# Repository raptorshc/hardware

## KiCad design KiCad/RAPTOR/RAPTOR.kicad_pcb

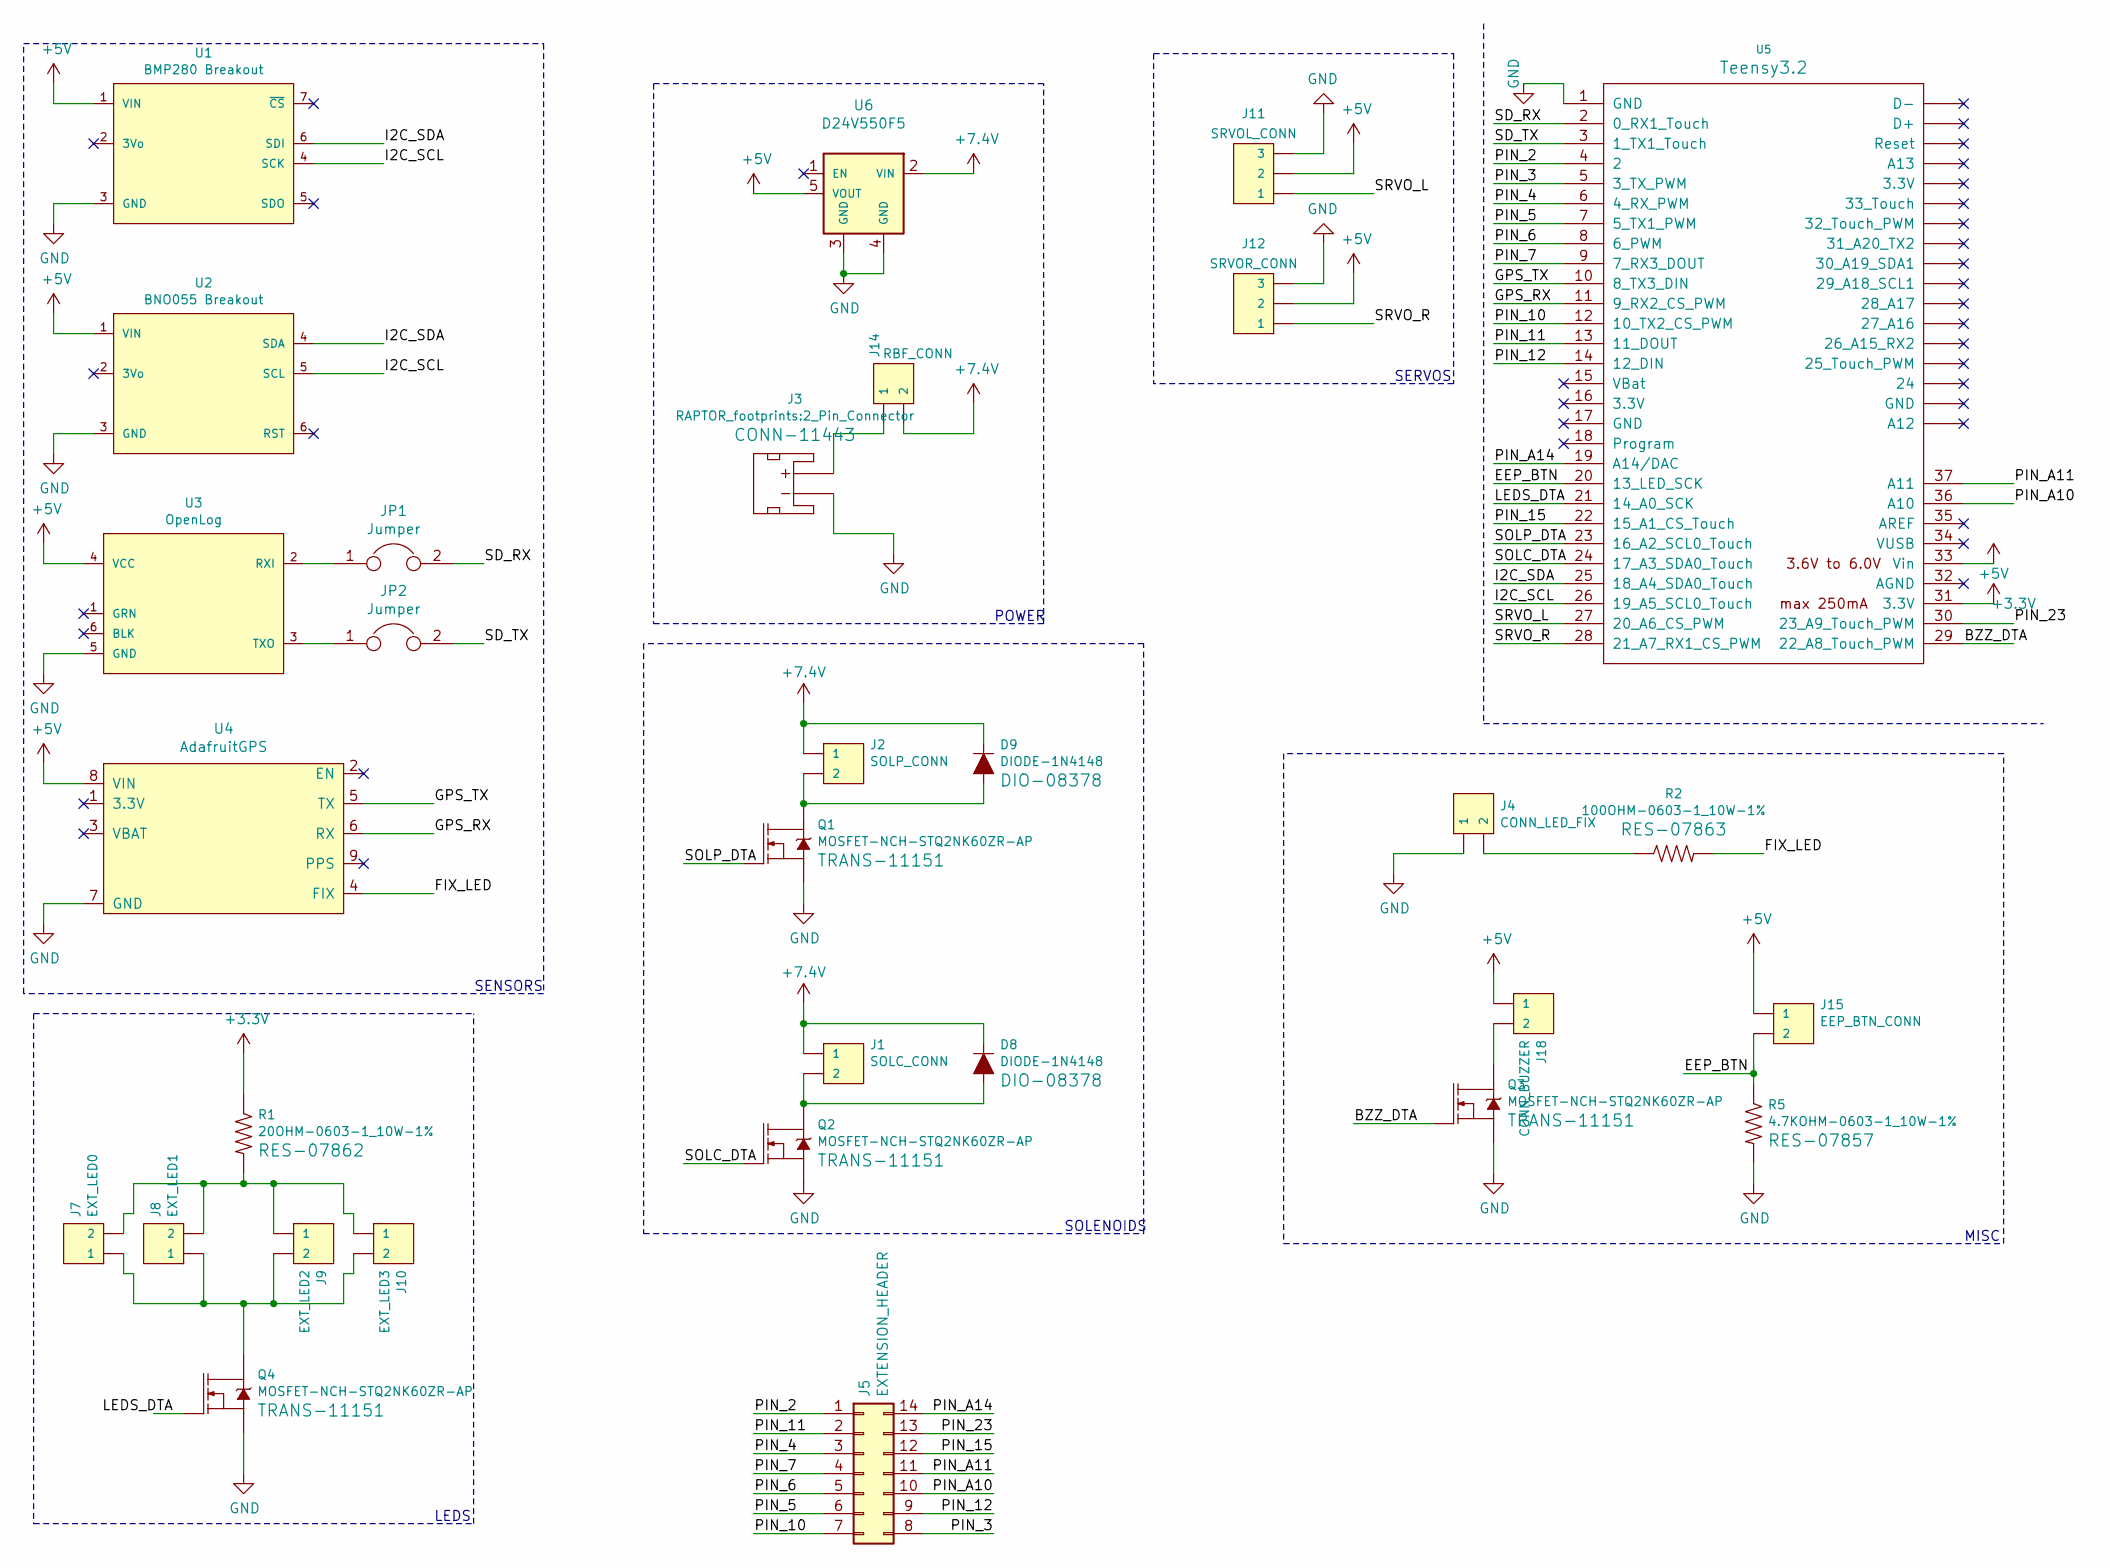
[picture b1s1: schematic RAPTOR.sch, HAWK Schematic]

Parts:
D8, D9: DIODE-1N4148
J1: SOLC_CONN; Molex-2pin
J2: SOLP_CONN; Molex-2pin
J3: JST_2MM_MALE; 2_Pin_Connector
J4: CONN_LED_FIX; Molex-2pin
J5: EXTENSION_HEADER; IDC-Header_2x07_P2.54mm_Vertical
J7: EXT_LED0; Molex-2pin
J8: EXT_LED1; Molex-2pin
J9: EXT_LED2; Molex-2pin
J10: EXT_LED3; Molex-2pin
J11: SRVOL_CONN; Molex-MOTOR
J12: SRVOR_CONN; Molex-MOTOR
J14: RBF_CONN; Molex-2pin
J15: EEP_BTN_CONN; Molex-2pin
J18: CONN_BUZZER; Molex-2pin
JP1, JP2: Jumper; Molex-2pin
Q1, Q2, Q3, Q4: MOSFET-NCH-STQ2NK60ZR-AP; MOSFET
R1: 20OHM-0603-1_10W-1%; Resistor
R2: 100OHM-0603-1_10W-1%; Resistor
R5: 4.7KOHM-0603-1_10W-1%; Resistor
U1: BMP280 Breakout; BMP280
U2: BNO055 Breakout; BNO055
U3: OpenLog
U4: AdafruitGPS
U5: Teensy3.2; Teensy30_31_32_LC
U6: D24V550F5; D24v50f5_Reg

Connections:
+3V3: R1.1, U5.31 (3.3V)
+5V: J11.2, J12.2, J15.1, J18.1, U1.1 (VIN), U2.1 (VIN), U3.4 (VCC), U4.8 (VIN), U5.33 (Vin), U6.5 (VOUT)
+7.5V: D8.C, D9.C, J1.1, J2.1, J14.2, U6.2 (VIN)
/BZZ_DTA: Q3.1 (G), U5.29 (22_A8_Touch_PWM)
/EEP_BTN: J15.2, R5.1, U5.20 (13_LED_SCK)
/FIX_LED: R2.2, U4.4 (FIX)
/GPS_RX: U4.6 (RX), U5.11 (9_RX2_CS_PWM)
/GPS_TX: U4.5 (TX), U5.10 (8_TX3_DIN)
/I2C_SCL: U1.4 (SCK), U2.5 (SCL), U5.26 (19_A5_SCL0_Touch)
/I2C_SDA: U1.6 (SDI), U2.4 (SDA), U5.25 (18_A4_SDA0_Touch)
/LEDS_DTA: Q4.1 (G), U5.21 (14_A0_SCK)
/PIN_2: J5.1, U5.4 (2)
/PIN_3: J5.8, U5.5 (3_TX_PWM)
/PIN_4: J5.3, U5.6 (4_RX_PWM)
/PIN_5: J5.6, U5.7 (5_TX1_PWM)
/PIN_6: J5.5, U5.8 (6_PWM)
/PIN_7: J5.4, U5.9 (7_RX3_DOUT)
/PIN_10: J5.7, U5.12 (10_TX2_CS_PWM)
/PIN_11: J5.2, U5.13 (11_DOUT)
/PIN_12: J5.9, U5.14 (12_DIN)
/PIN_15: J5.12, U5.22 (15_A1_CS_Touch)
/PIN_23: J5.13, U5.30 (23_A9_Touch_PWM)
/PIN_A10: J5.10, U5.36 (A10)
/PIN_A11: J5.11, U5.37 (A11)
/PIN_A14: J5.14, U5.19 (A14/DAC)
/SD_RX: JP1.2, U5.2 (0_RX1_Touch)
/SD_TX: JP2.2, U5.3 (1_TX1_Touch)
/SOLC_DTA: Q2.1 (G), U5.24 (17_A3_SDA0_Touch)
/SOLP_DTA: Q1.1 (G), U5.23 (16_A2_SCL0_Touch)
/SRVO_L: J11.1, U5.27 (20_A6_CS_PWM)
/SRVO_R: J12.1, U5.28 (21_A7_RX1_CS_PWM)
GND: J3.1 (-), J4.1, J11.3, J12.3, Q1.2 (S), Q2.2 (S), Q3.2 (S), Q4.2 (S), R5.2, U1.3 (GND), U2.3 (GND), U3.5 (GND), U4.7 (GND), U5.1 (GND), U6.3 (GND), U6.4 (GND)
unnamed: D8.A, J1.2, Q2.3 (D)
unnamed: D9.A, J2.2, Q1.3 (D)
unnamed: J4.2, R2.1
unnamed: J7.2, J8.2, J9.1, J10.1, R1.2
unnamed: J7.1, J8.1, J9.2, J10.2, Q4.3 (D)
unnamed: J3.2 (+), J14.1
unnamed: J18.2, Q3.3 (D)
unnamed: JP1.1, U3.2 (RXI)
unnamed: JP2.1, U3.3 (TXO)

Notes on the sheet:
SERVOS
SOLENOIDS
LEDS
POWER
MISC
SENSORS

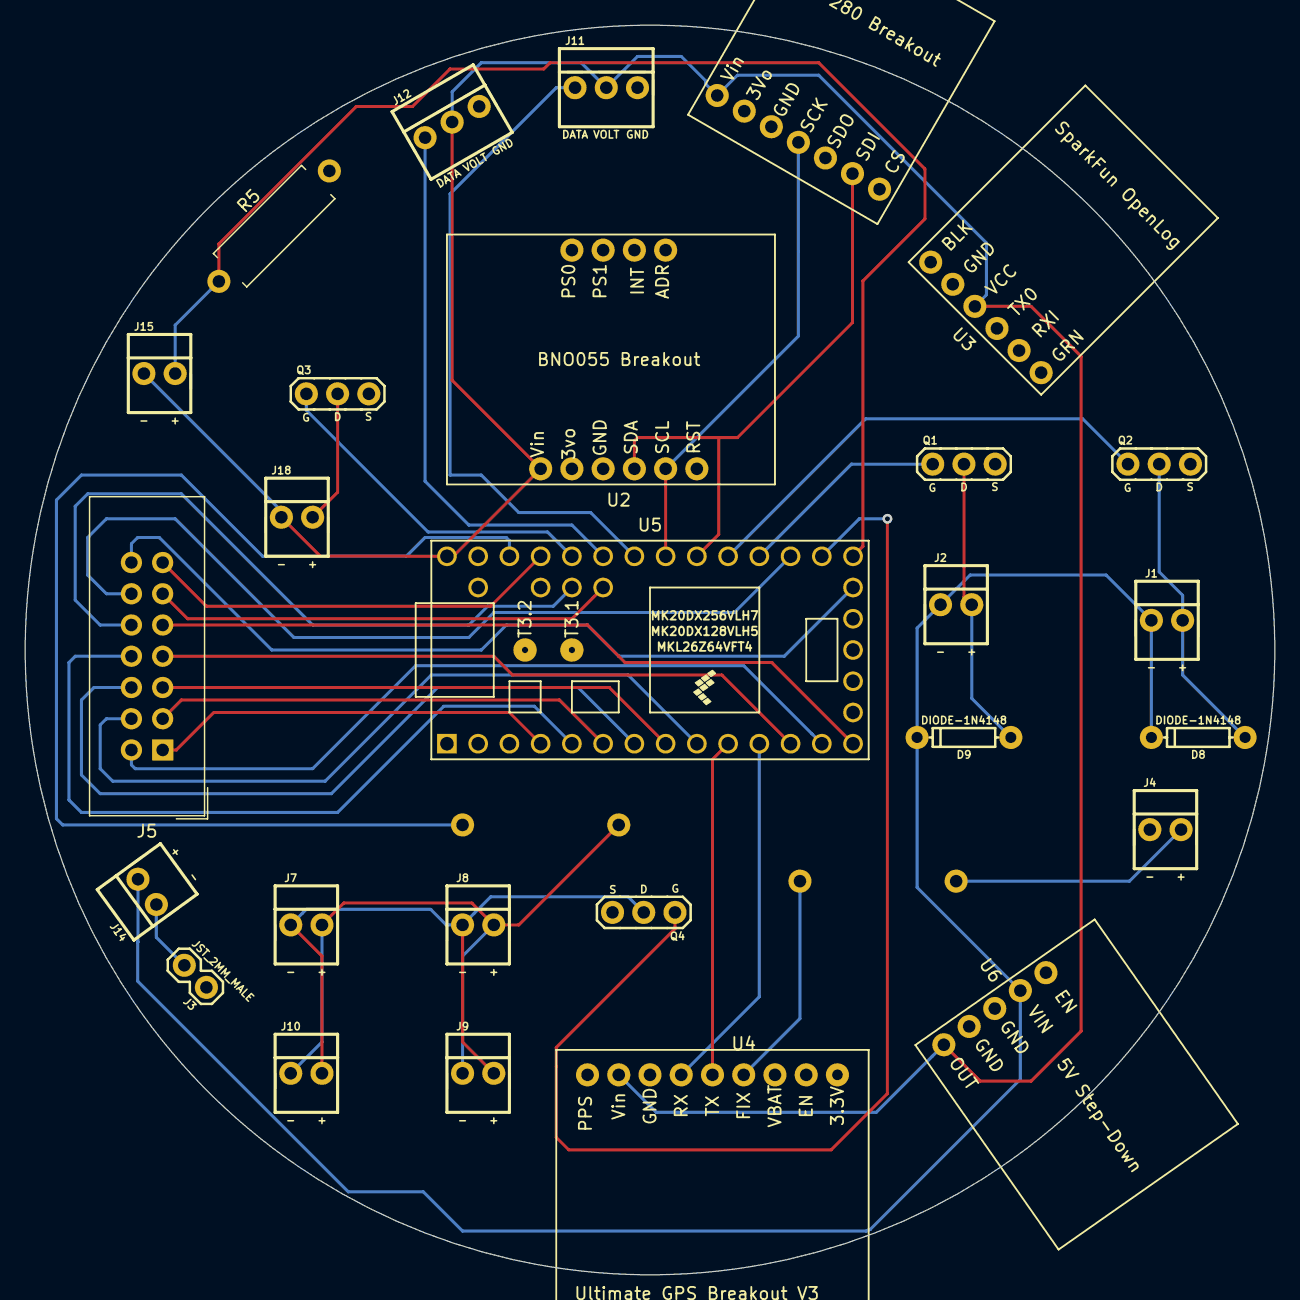
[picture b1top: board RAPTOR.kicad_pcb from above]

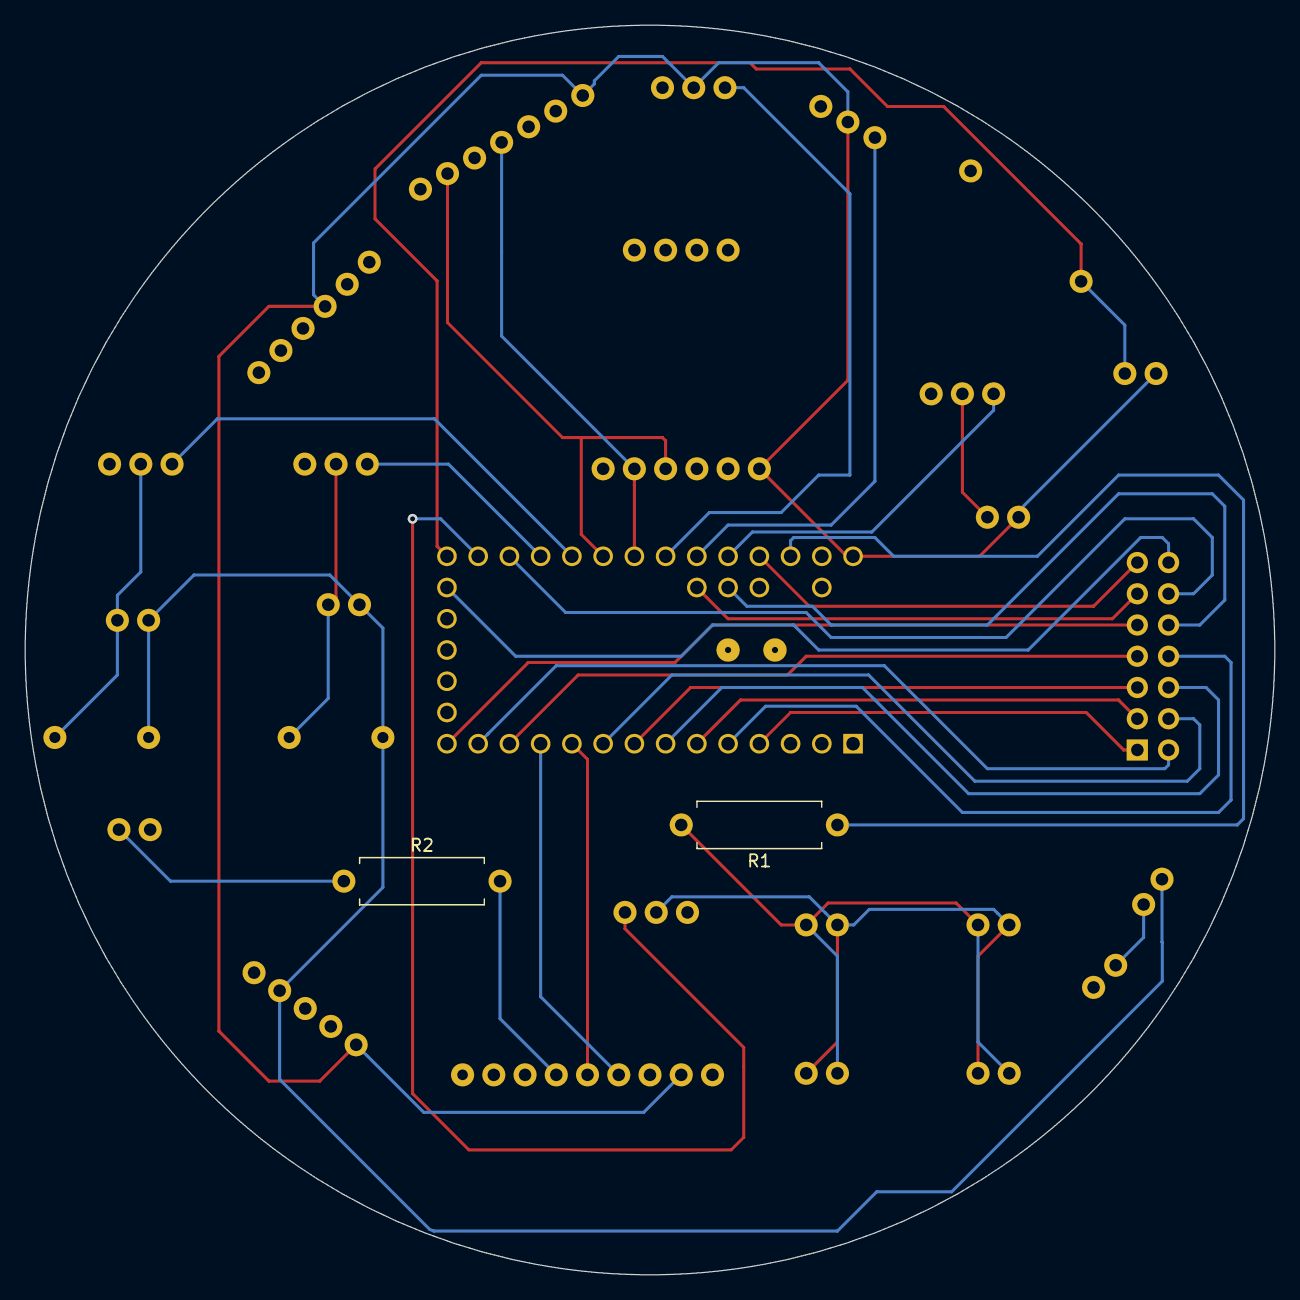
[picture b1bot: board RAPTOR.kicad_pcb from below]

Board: 2 copper layers, 101.6 x 101.6 mm, 29 parts (2 on the bottom side), 37 nets.

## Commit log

2018-10-25 new project from arduino uno template
2018-10-25 Revert "new project from arduino uno template"
    This reverts commit d8d94c75d211f8ad6141b76f4c75afd9c963bf61.
2018-10-25 create project from arduino mega template with gitignore
2018-10-25 add BMP280 and wiring
2018-10-26 make pcb
2018-10-26 add bmp footprint
2018-10-26 reorganize .gitignores to be more local
2018-10-26 generalize bak ignore
2018-10-26 add bmp footprint to pcb
2018-10-26 move to uno, re-add bmp
2018-10-26 add bno, start on footprint for bmp
2018-11-03 Attempted to Change the Bno005 Footprint - didn't go well
2018-11-03 create openlog symbol
2018-11-03 created adafruit gps
2018-11-03 small changes to gps symbol, add gps and openlog to schematic
2018-11-10 Added all the footprints and associated them with the symbols in the schematics
2018-11-10 fix sensor numbers, add servos, solenoids, leds, switches
2018-11-10 add net + pcb files
2019-01-12 Add voltage regulators, schematic pdf
2019-01-12 generate BoM
2019-01-12 Voltage Reg Footprints
    Created the voltage regulator footprint for he 12v reg
2019-01-12 Auto stash before merge of "hardware" and "origin/hardware"
2019-01-12 remove thing
2019-01-12 rev 0.5.5 schematic
2019-01-12 mosfet source to gnd + sol net label, removed second vreg
    Mosfet was hooked up to -12V, instead added a GND connection and in the middle of source and ground put a wire with a diode going out to a SOLP/C connection. Removed redundant voltage regulator (<0.7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
2019-01-15 resolves #57
2019-01-15 change battery to battery connector
2019-01-15 resolves #56
2019-01-15 add pulldown res, resolves #58
2019-01-15 add molex connectors for LEDs
2019-01-15 Arduango COnnecter Bois
2019-01-15 Customize Arduino Connectors, add names to net labels, resolve #59
    replace motors with molex connectors
2019-01-15 rev 0.6 final
2019-01-17 moved a single mosfet
2019-01-17 Fixed MOSFETS gate and drain on diagram
2019-01-17 commit libraries KiCad
2019-01-17 change to L4940V5
2019-01-17 change LED resistor values
2019-01-17 add a hotwire
    Needs correct labeling
2019-01-18 fix hotwire
2019-01-18 add RBF
2019-01-18 schematic rev 0.6.5
2019-01-18 added connectors for exterior LEDs in place of diodes
2019-01-18 change to D24V550F5
2019-01-18 change pdf
2019-01-18 make everything connectors
2019-01-18 New V_Reg Footpritnt
    The D24V50F5 has now been added to the Raptor Footprings
2019-01-18 remove capacitors from circuit
2019-01-18 put stuff on pcb thing
2019-01-18 extend board
2019-01-19 Fitted parts
    Placed all the compnents on the actual PCB not just off to the side
2019-01-19 PCB Error Fixing
    Changed footprints and symbols to be more accurate
2019-01-19 make pdf
2019-01-21 connect a gnd
2019-01-21 Test of mergy bois
    ^^^^
2019-01-21 Version 1 of fully wired PCB
    A preliminary full connection of the PCB board
2019-01-21 MOved PDF Because Sean is mean
    Version contrllled the PDF and such
2019-01-23 Widened PCB Board
    This should resolve something but IDK the number
2019-01-23 Revert "Widened PCB Board"
    This reverts commit 6127001810acaa0b6aebb6d9f1e36fbc48228c71.
2019-01-24 Revert "Revert "Widened PCB Board""
    This reverts commit edbbf49bd2c69fdd694dc2b23b572114c8313dd8.
2019-01-24 add connector for buzzer, resolves #72
2019-01-24 increase resistor footprint length
2019-01-24 DeTrced the boi
    See above
2019-01-24 Moved Breakouts to fully on board
    Yeet
2019-01-24 Route Test
2019-01-24 testing silk screen
2019-01-24 moved names on silkscreen and remove long names
2019-01-24 Trial Wireng V2
    Im probs gonna chage some stuff here
2019-01-24 Used many Vias
    Here we go
2019-01-24 Full Wire and Ground Fill
    Also got dem Vias dig dawg.
2019-01-24 Moved Screw Hole
    Hopefully is in the good spot
2019-01-24 fixed silk-screen names again
2019-01-24 updated phoenix PCB pdf diagram
2019-01-26 fix pdf, add png
2019-01-26 Update Mosfet Vals
    yeet yeet yeet yoote yeet yeet yeet yeet yoote yeet yeet yeet yeet yoote yeet yeet yeet yeet yoote yeet yeet yeet yeet yoote yeet
2019-01-26 oops
    yeah
2019-01-26 Update the PDF for Schemnatce
    Schematic Schematic Schemeatiscs
2019-01-26 Took racy pictures of the PCB
    Don't let them leak to the internet it could ruin her professional career
2019-01-26 Renamed the naughty pics
    Took out of the spaces AN
2019-01-30 move u1, u5 slightly
2019-02-11 generate step
2019-02-11 removed overlapping outlines
2019-02-11 Added CAD files for the PCB assembled with an Arduino Uno
2019-02-14 made changes to pcb I think
2019-02-22 Additional PCB CAD files
2019-02-22 This is the openlog
2019-02-28 remove routing
2019-02-28 3 pin to 2 pin, resolve #90
2019-02-28 Updates to Breakout Board Footprints
2019-02-28 Updates to Break Board Footprints
2019-02-28 move R2 and R3, resolves #88
2019-02-28 Add Labels to Arduino Uno Headers
2019-02-28 update pcb footprints
2019-02-28 Added footprint for 2-pin molex connector
2019-02-28 add sparkfun libraries
2019-02-28 Added Bird Logo to PCB
2019-02-28 merge
2019-02-28 add mosfet silkscreen, update pcb
2019-02-28 add 2 pin molex and motor silkscreen, resolves #92
2019-02-28 fix molex footprints
2019-02-28 change resistor hole sizes to be consistent
2019-02-28 Organized PCB Layout
2019-03-01 Adjust 1 board
2019-03-01 add buttons to rx and tx lines
2019-03-01 Start the Routing
    Lets Go dude
2019-03-01 All Routed w/o RXTX button
    All the connections are made except for the rx and tx button
2019-03-01 change switch with jumper
2019-03-01 make jumper just two pin holes
2019-03-01 Finished Roouting
    Needs checking though. Full error and netlist tests
2019-03-01 BIRD
    BIRD
2019-03-01 did some stuff
2019-03-01 flip some + and - signs
2019-03-01 move labels for motors
2019-04-08 update schematic pdf, pcb picture
2019-07-14 do schematic for thunderbird
2019-07-18 update schematic, remove some leds and eeprom button
2019-08-24 Created hawk electrical branch. Created ltspice schematic.
2019-08-24 Moved pcb files to KiCad folder
2019-09-14 Added Teensy Footprints
    Put the stuff in the other stuff
2019-09-14 Added Teensy
2019-09-14 Removed 12v Step Up from schematic.
2019-09-16 Swapped +12V references with +7.4V references.
2019-09-16 Removed unused hotwire subcircuit.
2019-09-21 reorganize some things on schematic
2019-09-21 make new pcb, add from netlist, phoenix now in phoenix.kicad_pcb
2019-09-21 Manuvered Componets as Such
    Made the PCB kinda organzed
2019-09-21 box groups, add extension header for unused teensy pins, fix some issues
2019-09-21 add to gitignore
2019-09-28 IDK what this does
2019-09-28 Revert "IDK what this does"
    This reverts commit 09bbb435101a955ba1c15fd4dfdde6fe15a208ff.
2019-09-28 Flipped Pin A11 and Pin 23
2019-09-28 Pin musical chairs
2019-09-28 pin musical chairs lightning roud
2019-09-28 Updated schematic page settings for Hawk
2019-09-28 Routed The Headder
    Got the pins where I wanted them to make routing easeir
2019-09-28 Routed Board no Ground Fill
    as seen
2019-09-28 The Real no ground fill
